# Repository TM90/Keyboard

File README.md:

# DIY Mechanical Keyboard

## Main Idea:

Have as much as possible open source? Also the tools used to build the keyboard

## Tool usage:
1. KiCAD (schematic, layout) (http://kicad.org/ )
2. avr-gcc (https://gcc.gnu.org/wiki/avr-gcc )
3. Export data for alu body from a layer in the KiCAD layout data

## Electronic
Own layout and schematic but based on this project to keep compatibility with tmk firmware and qmk firmware:

<https://github.com/tmk/HHKB_controller/blob/master/schematic/HHKB_controller_revG.pdf>

### Datasheets

#### Power
- LM1117 3.3V LDO http://cdn-reichelt.de/documents/datenblatt/A200/LM1117-TI.pdf
- NCP1402 step up DCDC Converter https://www.onsemi.com/pub/Collateral/NCP1402-D.PDF ->farnell: out of production
      - Alternative MAX1724 https://www.mouser.de/datasheet/2/256/MAX1722-MAX1724-97057.pdf but no Kicad Lib yet
- MCP 73831/2 Single Cell Lipo Charge Management Controller http://ww1.microchip.com/downloads/en/DeviceDoc/20001984g.pdf

#### Bluetooth
- RN42 Bluetooth Module http://ww1.microchip.com/downloads/en/DeviceDoc/50002328A.pdf

#### Microcontroller
- ATMEGA32U4 8 bit Microcontroller with USB http://ww1.microchip.com/downloads/en/devicedoc/atmel-7766-8-bit-avr-atmega16u4-32u4_datasheet.pdf
- AT90USB1286 8 bit Microcontroller with USB but more IO than ATMEGA32U4  http://ww1.microchip.com/downloads/en/DeviceDoc/doc7593.pdf

## Mechanical
<http://builder.swillkb.com/>

Sandwich case or alu bend case

## Software/Firmware
- <https://qmk.fm/>
- <https://github.com/tmk/tmk_keyboard>

## Other:
<http://www.keyboard-layout-editor.com/#/>

Prototype for Switches without big PCB and description how to build a small keyboard:
<https://learn.sparkfun.com/tutorials/cherry-mx-switch-breakout-hookup-guide>

Fullsize Keyboard matrix example with atmega32u4:
<https://easyeda.com/farmakon/GH80_3000-4f3cee521afd4be3858c4b5cc3b76f9e>

## Manufacturer:
### PCB:
- beta layout <https://de.beta-layout.com/leiterplatten/> 
- LiteOn <https://www.leiton.de/index.html> 
- jlcpcb <https://jlcpcb.com/>
### Mechanical:
Maybe using a front panel service for the keyboard front, aluminum or acrylic would be possible at beta layout

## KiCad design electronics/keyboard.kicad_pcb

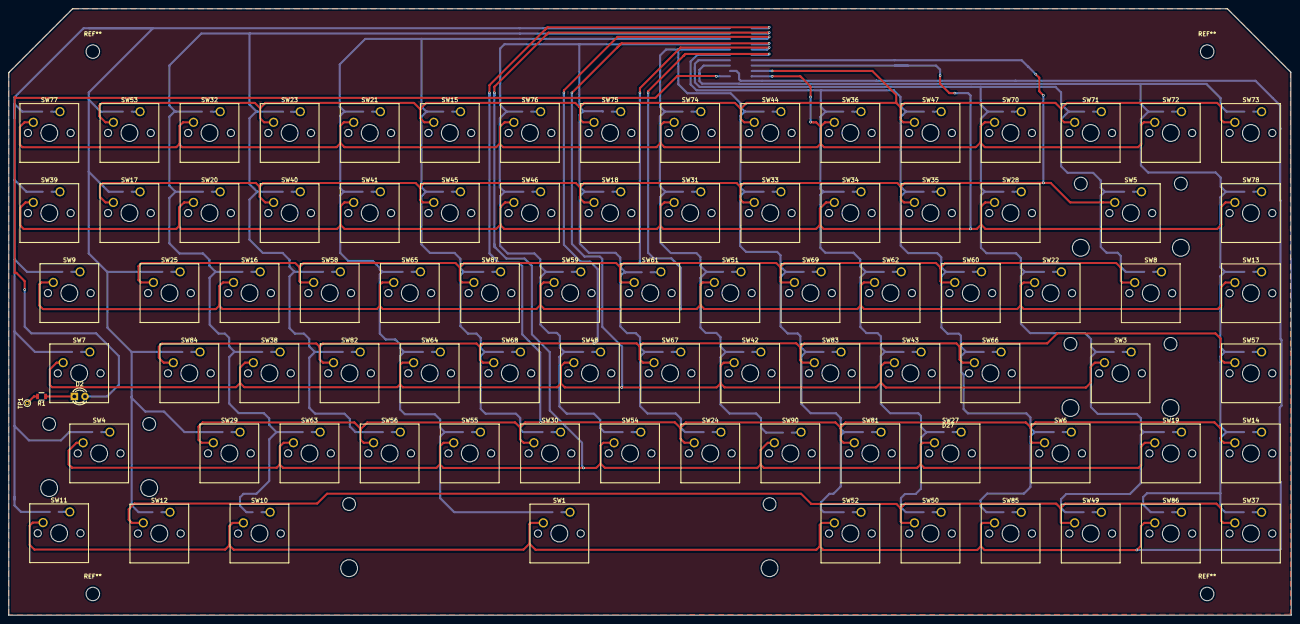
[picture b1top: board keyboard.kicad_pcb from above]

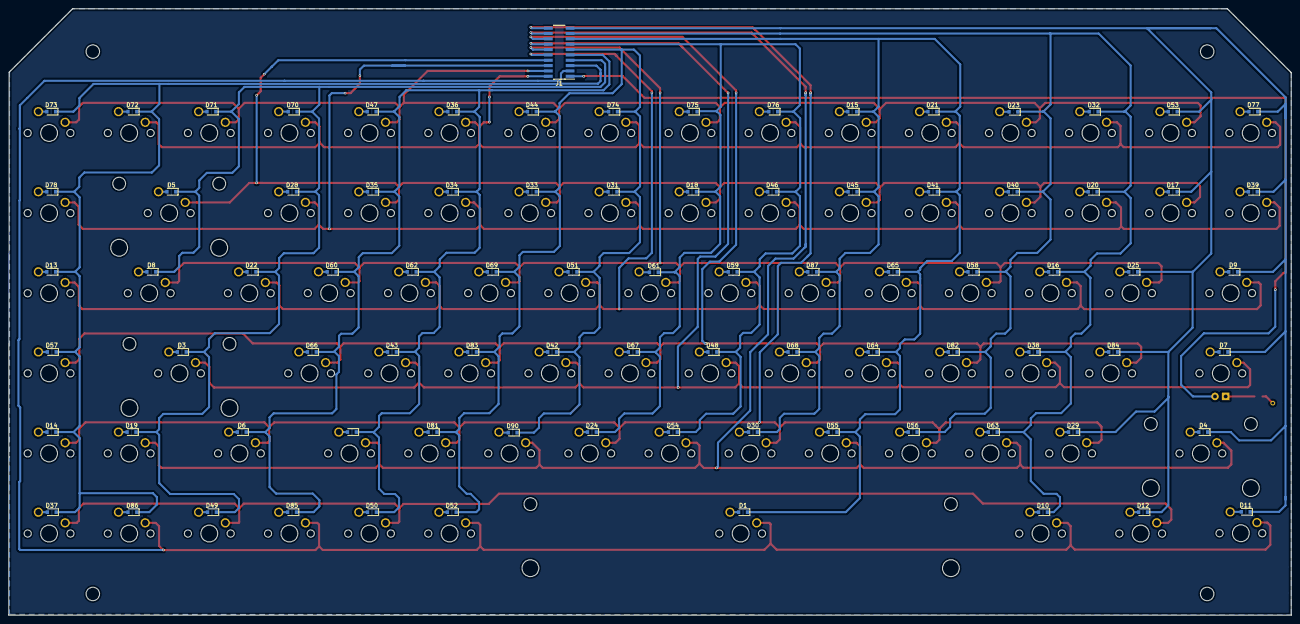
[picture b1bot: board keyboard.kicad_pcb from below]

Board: 2 copper layers, 305.0 x 144.2 mm, 172 parts (85 on the bottom side), 107 nets.

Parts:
D1, D3, D4, D5, D6, D7, D8, D9, D10, D11, D12, D13, D14, D15, D16, D17, D18, D19, D20, D21, D22, D23, D24, D25, D27, D28, D29, D30, D31, D32, D33, D34, D35, D36, D37, D38, D39, D40, D41, D42, D43, D44, D45, D46, D47, D48, D49, D50, D51, D52, D53, D54, D55, D56, D57, D58, D59, D60, D61, D62, D63, D64, D65, D66, D67, D68, D69, D70, D71, D72, D73, D74, D75, D76, D77, D78, D81, D82, D83, D84, D85, D86, D87, D90: D; D_0805
D2: LED; LED_D3.0mm
J1: CONN_02X10; Pin_Header_Straight_2x10_Pitch1.27mm_SMD
R1: 10k; R_0805
SW1: SW_Push; SW_Cherry_MX1A_6.25u_PCB
SW3, SW4: SW_Push; SW_Cherry_MX1A_2.25u_PCB
SW5: SW_Push; SW_Cherry_MX1A_2.00u_PCB
SW6, SW7: SW_Push; SW_Cherry_MX1A_1.75u_PCB
SW8, SW9: SW_Push; SW_Cherry_MX1A_1.50u_PCB
SW10, SW11, SW12: SW_Push; SW_Cherry_MX1A_1.25u_PCB
SW13, SW14, SW15, SW16, SW17, SW18, SW19, SW20, SW21, SW22, SW23, SW24, SW25, SW27, SW28, SW29, SW30, SW31, SW32, SW33, SW34, SW35, SW36, SW37, SW38, SW39, SW40, SW41, SW42, SW43, SW44, SW45, SW46, SW47, SW48, SW49, SW50, SW51, SW52, SW53, SW54, SW55, SW56, SW57, SW58, SW59, SW60, SW61, SW62, SW63, SW64, SW65, SW66, SW67, SW68, SW69, SW70, SW71, SW72, SW73, SW74, SW75, SW76, SW77, SW78, SW81, SW82, SW83, SW84, SW85, SW86, SW87, SW90: SW_Push; SW_Cherry_MX1A_1.00u_PCB
TP1: TestPoint; PINTST

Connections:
/PA0: D4.1, D7.1, D9.1, D11.1, D12.1, D17.1, D25.1, D29.1, D39.1, D53.1, D77.1, D84.1, J1.19
/PA1: D10.1, D16.1, D20.1, D23.1, D32.1, D38.1, D40.1, D56.1, D58.1, D63.1, D82.1, J1.17
/PA2: D1.1, D15.1, D21.1, D30.1, D41.1, D45.1, D55.1, D64.1, D65.1, D68.1, D87.1, J1.15
/PA3: D18.1, D24.1, D46.1, D48.1, D54.1, D59.1, D61.1, D67.1, D75.1, D76.1, J1.13
/PA4: D31.1, D33.1, D42.1, D44.1, D51.1, D52.1, D69.1, D74.1, D81.1, D83.1, D90.1, J1.11
/PA5: D6.1, D27.1, D34.1, D35.1, D36.1, D43.1, D47.1, D50.1, D60.1, D62.1, D66.1, D85.1, J1.9
/PA6: D3.1, D5.1, D8.1, D19.1, D22.1, D28.1, D49.1, D70.1, D71.1, J1.7
/PA7: D13.1, D14.1, D37.1, D57.1, D72.1, D73.1, D78.1, D86.1, J1.5
/PB0: J1.2, SW21.2, SW32.2, SW36.2, SW70.2, SW72.2, SW74.2, SW76.2, SW77.2
/PB1: J1.4, SW15.2, SW23.2, SW44.2, SW47.2, SW53.2, SW71.2, SW73.2, SW75.2
/PB2: J1.6, SW20.2, SW28.2, SW31.2, SW34.2, SW39.2, SW41.2, SW46.2, SW78.2
/PB3: J1.8, SW5.2, SW17.2, SW18.2, SW33.2, SW35.2, SW40.2, SW45.2
/PB4: J1.10, SW9.2, SW13.2, SW16.2, SW22.2, SW51.2, SW59.2, SW62.2, SW65.2
/PB5: J1.12, SW8.2, SW25.2, SW58.2, SW60.2, SW61.2, SW69.2, SW87.2
/PB6: J1.14, SW3.2, SW7.2, SW38.2, SW42.2, SW43.2, SW48.2, SW64.2
/PB7: J1.16, SW57.2, SW66.2, SW67.2, SW68.2, SW82.2, SW83.2, SW84.2
/PC0: J1.18, SW4.2, SW19.2, SW27.2, SW54.2, SW55.2, SW63.2, SW90.2
/PC1: J1.20, SW6.2, SW14.2, SW24.2, SW29.2, SW30.2, SW56.2, SW81.2
/PC2: J1.3, SW1.2, SW10.2, SW11.2, SW52.2, SW85.2, SW86.2
/SwitchMatrix/COL11: SW12.2, SW37.2, SW49.2, SW50.2
unnamed: D1.2, SW1.1
unnamed: D2.1, R1.1
unnamed: D2.2, J1.1
unnamed: D3.2, SW3.1
unnamed: D4.2, SW4.1
unnamed: D5.2, SW5.1
unnamed: D6.2, SW6.1
unnamed: D7.2, SW7.1
unnamed: D8.2, SW8.1
unnamed: D9.2, SW9.1
unnamed: D10.2, SW10.1
unnamed: D11.2, SW11.1
unnamed: D12.2, SW12.1
unnamed: D13.2, SW13.1
unnamed: D14.2, SW14.1
unnamed: D15.2, SW15.1
unnamed: D16.2, SW16.1
unnamed: D17.2, SW17.1
unnamed: D18.2, SW18.1
unnamed: D19.2, SW19.1
unnamed: D20.2, SW20.1
unnamed: D21.2, SW21.1
unnamed: D22.2, SW22.1
unnamed: D23.2, SW23.1
unnamed: D24.2, SW24.1
unnamed: D25.2, SW25.1
unnamed: D27.2, SW27.1
unnamed: D28.2, SW28.1
unnamed: D29.2, SW29.1
unnamed: D30.2, SW30.1
unnamed: D31.2, SW31.1
unnamed: D32.2, SW32.1
unnamed: D33.2, SW33.1
unnamed: D34.2, SW34.1
unnamed: D35.2, SW35.1
unnamed: D36.2, SW36.1
unnamed: D37.2, SW37.1
unnamed: D38.2, SW38.1
unnamed: D39.2, SW39.1
unnamed: D40.2, SW40.1
unnamed: D41.2, SW41.1
unnamed: D42.2, SW42.1
unnamed: D43.2, SW43.1
unnamed: D44.2, SW44.1
unnamed: D45.2, SW45.1
unnamed: D46.2, SW46.1
unnamed: D47.2, SW47.1
unnamed: D48.2, SW48.1
unnamed: D49.2, SW49.1
unnamed: D50.2, SW50.1
unnamed: D51.2, SW51.1
unnamed: D52.2, SW52.1
unnamed: D53.2, SW53.1
unnamed: D54.2, SW54.1
unnamed: D55.2, SW55.1
unnamed: D56.2, SW56.1
unnamed: D57.2, SW57.1
unnamed: D58.2, SW58.1
unnamed: D59.2, SW59.1
unnamed: D60.2, SW60.1
unnamed: D61.2, SW61.1
unnamed: D62.2, SW62.1
unnamed: D63.2, SW63.1
unnamed: D64.2, SW64.1
unnamed: D65.2, SW65.1
unnamed: D66.2, SW66.1
unnamed: D67.2, SW67.1
unnamed: D68.2, SW68.1
unnamed: D69.2, SW69.1
unnamed: D70.2, SW70.1
unnamed: D71.2, SW71.1
unnamed: D72.2, SW72.1
unnamed: D73.2, SW73.1
unnamed: D74.2, SW74.1
unnamed: D75.2, SW75.1
unnamed: D76.2, SW76.1
unnamed: D77.2, SW77.1
unnamed: D78.2, SW78.1
unnamed: D81.2, SW81.1
unnamed: D82.2, SW82.1
unnamed: D83.2, SW83.1
unnamed: D84.2, SW84.1
unnamed: D85.2, SW85.1
unnamed: D86.2, SW86.1
unnamed: D87.2, SW87.1
unnamed: D90.2, SW90.1
unnamed: R1.2, TP1.1

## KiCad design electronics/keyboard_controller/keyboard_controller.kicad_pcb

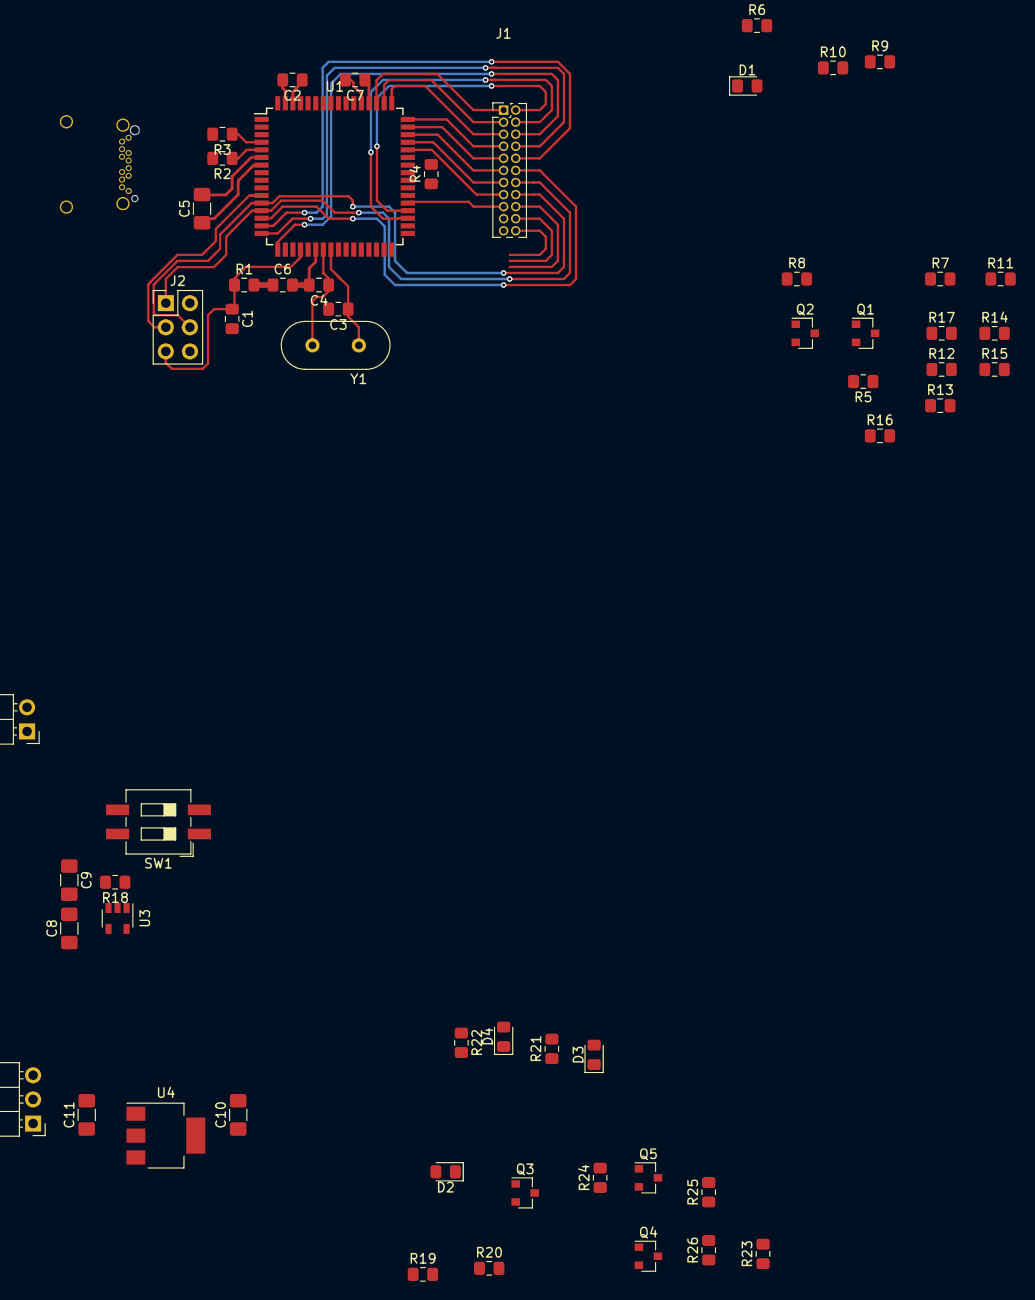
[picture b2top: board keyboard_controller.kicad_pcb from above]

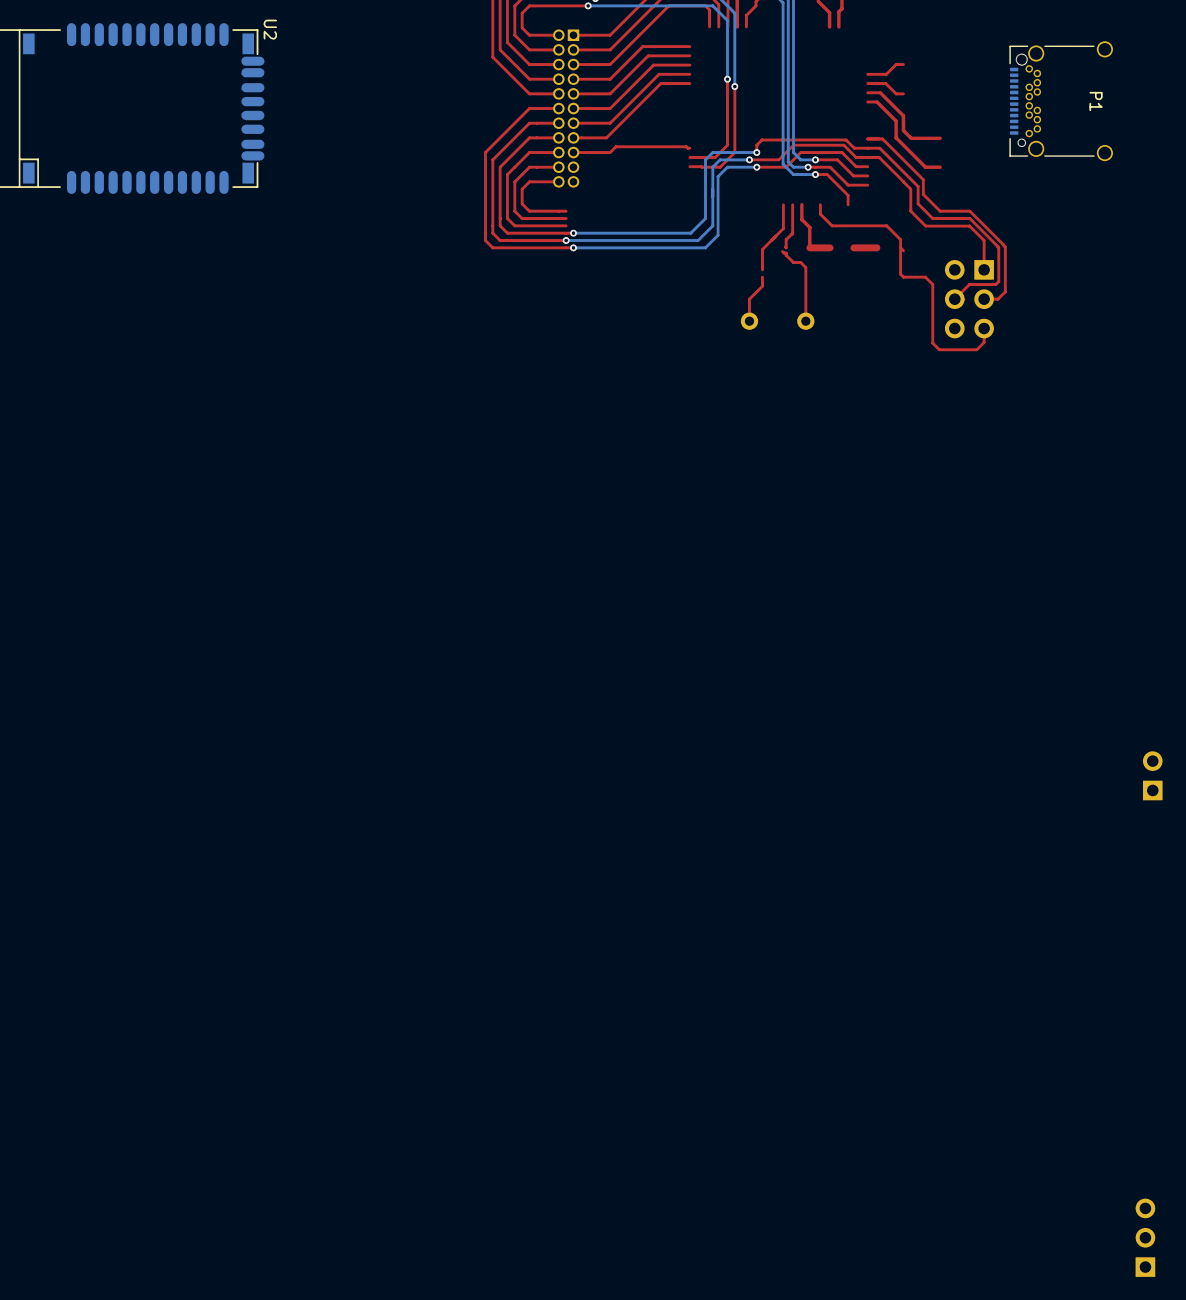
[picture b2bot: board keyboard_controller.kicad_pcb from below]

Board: 2 copper layers, 57 parts (2 on the bottom side), 62 nets.

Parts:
C1, C2, C6, C7: 100n; C_0805_2012Metric_Pad1.15x1.40mm_HandSolder
C3, C4: 22p; C_0805_2012Metric_Pad1.15x1.40mm_HandSolder
C5: 1u; C_1206_3216Metric_Pad1.42x1.75mm_HandSolder
C8, C9: 4u7; C_1206_3216Metric_Pad1.42x1.75mm_HandSolder
C10, C11: 10u; C_1206_3216Metric_Pad1.42x1.75mm_HandSolder
D1, D3, D4: LED; LED_0805_2012Metric_Pad1.15x1.40mm_HandSolder
D2: D_Schottky; D_0805_2012Metric_Pad1.15x1.40mm_HandSolder
J1: Conn_02x11_Odd_Even; PinHeader_2x11_P1.27mm_Vertical
J2: AVR-ISP-6; PinHeader_2x03_P2.54mm_Vertical
J3: Conn_01x02_Male; PinHeader_1x02_P2.54mm_Horizontal
J4: Conn_01x03_Male; PinHeader_1x03_P2.54mm_Horizontal
P1: USB_C_Plug_USB2.0; USB_C_Receptacle_Amphenol_12401548E4-2A_CircularHoles
Q1, Q2, Q4: Q_NMOS_DGS; SOT-23
Q3, Q5: Q_PMOS_DGS; SOT-23
R1, R4, R6, R19, R21, R22: 1k; R_0805_2012Metric_Pad1.15x1.40mm_HandSolder
R2, R3: 22; R_0805_2012Metric_Pad1.15x1.40mm_HandSolder
R5, R7, R8, R10, R11, R12, R14, R16, R20, R23, R24, R25, R26: 10k; R_0805_2012Metric_Pad1.15x1.40mm_HandSolder
R9: 0; R_0805_2012Metric_Pad1.15x1.40mm_HandSolder
R13, R15, R17: 15k; R_0805_2012Metric_Pad1.15x1.40mm_HandSolder
R18: PROG; R_0805_2012Metric_Pad1.15x1.40mm_HandSolder
SW1: SW_DPST; SW_DIP_SPSTx02_Slide_6.7x6.64mm_W8.61mm_P2.54mm_LowProfile
U1: AT90USB1286-AU; TQFP-64_14x14mm_P0.8mm
U2: RN42
U3: MCP73832-3-OT; SOT-23-5
U4: LM1117-3.3; SOT-223-3_TabPin2
Y1: 16MHz; Crystal_HC49-4H_Vertical

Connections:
+3V3: Q1.2, Q2.2, R5.2, R6.2, R8.2, R10.1, SW1.2, U2.11
+5V: C6.1, C7.1, C10.1, J2.2, J4.1, R1.2, R7.1, R11.1, U1.21, U1.52, U1.64, U4.3
/AREF: C2.1, U1.62
/CONN: R12.1, R13.2, U2.3
/DMINUS: P1.A7, R3.2
/DPLUS: P1.A6, R2.2
/FACTORY_RESET: R9.2, U2.22
/LED_STS: D1.1, U2.21
/LINKED: U1.55, U2.19
/MCU_RX: Q1.1, R7.2, U1.27
/MCU_TX: R14.2, U1.28
/PA0: J1.1, U1.51
/PA1: J1.3, U1.50
/PA2: J1.5, U1.49
/PA3: J1.7, U1.48
/PA4: J1.9, U1.47
/PA5: J1.11, U1.46
/PA6: J1.13, U1.45
/PA7: J1.15, U1.44
/PB0: J1.20, U1.10
/PB1: J1.18, J2.3, U1.11
/PB2: J1.16, J2.4, U1.12
/PB3: J1.14, J2.1, U1.13
/PB4: J1.12, U1.14
/PB5: J1.10, U1.15
/PB6: J1.8, U1.16
/PB7: J1.6, U1.17
/PC0: J1.4, U1.35
/PC1: J1.2, U1.36
/PC2: J1.17, U1.37
/PC3: J1.22, U1.38
/PD5: R16.2, U1.30
/PF0: R25.1, R26.2, U1.61
/PF1: Q2.1, R11.2, U1.60
/PF4: Q4.2, R23.2, U1.57
/PF7: R12.2, U1.54
/RESET: C1.1, J2.5, R1.1, U1.20
/RN42_CTS: R16.1, R17.2, U2.16
/RN42_RTS: Q2.3, R8.1, U2.15
/RN42_RX: R14.1, R15.2, U2.13
/RN42_TX: Q1.3, R5.1, U2.14
/Sheet5D061573/Chrg: D4.1, U3.1
/Sheet5D061573/LIPO_RAW: C9.1, J3.1, Q5.1, R24.2, SW1.3, U3.3
/Sheet5D061573/LIPO_SW: Q3.3, SW1.4
/Sheet5D061573/PSEL: D2.1, J4.3, Q3.1, R22.2
/Sheet5D061573/Vout33_int: C11.1, SW1.1, U4.2
/VUSB: C8.1, D2.2, P1.A4, P1.A9, P1.B4, P1.B9, R19.2, R21.2, U1.3, U1.8, U3.4
GND: C1.2, C2.2, C3.2, C4.2, C5.2, C6.2, C7.2, C8.2, C9.2, C10.2, C11.2, D3.1, J1.21, J2.6, J3.2, J4.2, P1.A1, P1.A12, P1.B1, P1.B12, P1.S1, Q4.3, R4.1, R13.1, R15.1, R17.1, R18.2, R20.1, R23.1, R26.1, U1.6, U1.22, U1.53, U1.63, U2.1, U2.12, U2.28, U2.29, U2.36, U3.2, U4.1
unnamed: C3.1, U1.24, Y1.1
unnamed: C4.1, U1.23, Y1.2
unnamed: C5.1, U1.7
unnamed: D1.2, R6.1
unnamed: D3.2, R21.1
unnamed: D4.2, R22.1
unnamed: Q3.2, R19.1, R20.2
unnamed: Q4.1, Q5.2, R24.1
unnamed: Q5.3, R25.2
unnamed: R2.1, U1.5
unnamed: R3.1, U1.4
unnamed: R4.2, U1.43
unnamed: R9.1, R10.2
unnamed: R18.1, U3.5

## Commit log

2018-06-09 Added README.md with first draft.
2018-06-10 Added on link for firmware
    And made markdown pandoc compatible
2018-06-10 Added gitignore with editor temp files
2018-07-02 Added link for Cherry MX switch breakout board.
2018-07-06 Update README.md
    Added links to used Datasheets
2018-07-06 Added initial Schematic
    - Todo
    - Add Bluetooth Module
    - Add Lipo Power Supply
    - connect switch matrix
2018-07-06 Updated .gitignore to ignore kicad backups and other temp files
2018-07-06 Added some structure to the schematics`
2018-07-07 Updated Structure
    - ISP programmer is now on interface sheet
    - added en and decoder to SwitchMatrix sheet
2018-07-07 Added Reset circuit and decap for en and decoders
2018-07-21 Added NCP1402
2018-07-21 Added Lipo Charge Controller
2018-07-21 Added additional Supply for remote usage.
    Started working on Bluetooth `
2018-07-21 Added Bluetoothmodule
    Now only the switch matrix is missing
2018-07-23 Added matrix schematic example
2018-08-10 Added Teensy 2.0 compatible controller datasheet
    Added the AT90USB1286
2018-08-10 Changed Controller to AT90USB now the additional circuitry at the matrix can be removed
2018-08-10 removed en and decoder from matrix now the controls are direct
2018-08-10 Finished the matrix
    Now the schematic should be at an initial finished point
2018-08-11 Annotated the schematics...
    Did a first ERC run looked fine...
2018-08-11 create an initial netlist and started assigning the footprints
2018-08-25 Started placement step
2018-08-25 Seperated the Buttons from the rest
2018-08-25 Seperated diodes
2018-08-25 seperated elements for the controller
2018-08-25 Clustured Suplly Circuitry
2018-08-27 Seperated elements in a sane way...
2018-08-29 Updated the usb connector to micro usb at the momement because it is in the lib
2018-08-29 Started working on the switches placements
2018-09-16 Worked on Placement changed the mothod to do it...
2018-09-16 Placement progress now only 1u elements left for placment of the switch matrix
2018-09-16 Initial Placement for the switches
2018-09-22 Placed Diodes and Main controller
2018-09-22 Added dimension as indecator
2018-10-10 Changed keyboard schematic since now keyboard and controller will be seperated
2018-10-12 Placed everthing again :(
2018-10-12 Started routing for this the schematic also gets restructured
2018-10-12 routed another row
2018-10-12 routed the 2nd column
2018-10-13 Added two columns
2018-10-13 Worked further on the layout
2018-10-13 more layout
2018-10-21 worked further on interconnect
2018-10-21 Further work on interconnect
2018-10-21 Another ROW layouted
2018-10-21 Finished Row layout
    Todo:
    - Route the last columns
    - change some layers in the layout (diodes, connector)
    - add fill
2018-10-22 routed two columns
2018-10-22 Added another column 3 left
2018-10-24 Added another column 2 to go
2018-10-25 Signal Routing done!
    Todo:
    - Area Fill
    - change the layers of rows and columns to swap the diodes away from
    the top
2018-10-30 Device Cleanup:
    Todo:
    - Fill areas
    - change layers of diodes
2018-10-30 Changed layers for the routes now diodes have to be moved to the other side
2018-10-30 Updated connector placed the diodes on the right side.
    Todo:
    - Area fill
    - some routing to the connector
2018-10-31 Corrected some footprints worked on connector routing 4 pins to go...
2018-10-31 Initial complete signal routing of the connector
2019-01-05 Fixed strange drc errors with replacing vias
2019-01-06 Added outline and some drill holes
    todo:
    - Additional 2 drill holes
    - update fill zones
    - add led for shift switch
2019-01-06 updated pcb
2019-01-06 Update keyboard.kicad_pcb
    Updated Via size
    Fixed fill area size
    Todo:
    - 2 additional drill holes
    - led for shift
2019-01-07 kicad5 fix and shift led in schematic
    - Fixed schematic for kicad5
    - added shift led in schematic
    Todo
    - Layout the led
2019-01-08 Updated PCB
    Initial finished version
2019-01-08 Added PCB outline in edge cut layer
2019-07-28 Added initial keyboard controller schematic
2019-07-28 Fixed some minor issues in the keyboard controller schematics
    Started placement for the layout
2019-12-08 Worked on Placement
2020-08-08 Worked no keyboard controller layout
2021-11-08 Update README.md
    https://forum.kicad.info/t/warning-avoid-all-links-to-kicad-pcb-org-use-kicad-org/31521
